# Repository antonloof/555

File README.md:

# 555 timer

A (or two actully) 555 timer made from some junk found in drawers

Could become a future "learn to PCB" project

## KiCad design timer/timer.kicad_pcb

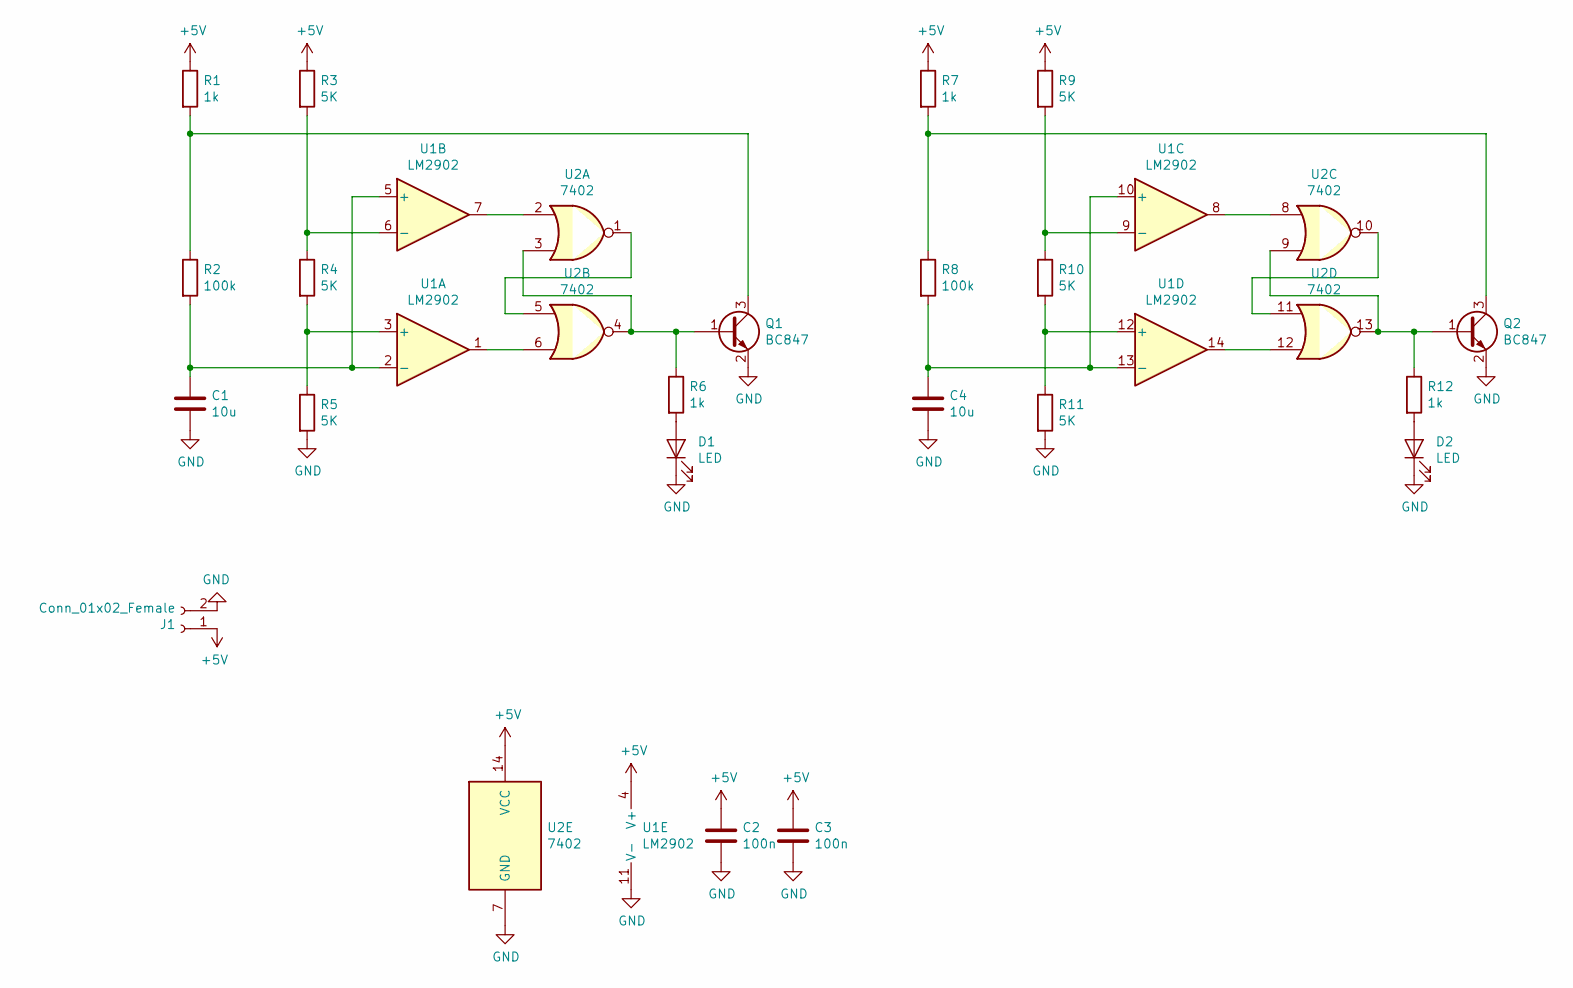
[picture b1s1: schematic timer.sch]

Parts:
C1, C4: 10u; C_0805_2012Metric_Pad1.15x1.40mm_HandSolder
C2, C3: 100n; C_0805_2012Metric_Pad1.15x1.40mm_HandSolder
D1, D2: LED; LED_1206_3216Metric_Pad1.42x1.75mm_HandSolder
J1: Conn_01x02_Female; TerminalBlock_Altech_AK300-2_P5.00mm
Q1, Q2: BC847; SOT-323_SC-70_Handsoldering
R1, R6, R7, R12: 1k; C_0805_2012Metric_Pad1.15x1.40mm_HandSolder
R2, R8: 100k; C_0805_2012Metric_Pad1.15x1.40mm_HandSolder
R3, R4, R5, R9, R10, R11: 5K; C_0805_2012Metric_Pad1.15x1.40mm_HandSolder
U1: LM2902; TSSOP-14_4.4x5mm_P0.65mm
U2: 7402; DIP-14_W7.62mm

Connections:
+5V: C2.1, C3.1, J1.1, R1.1, R3.1, R7.1, R9.1, U1.4 (V+), U2.14 (VCC)
GND: C1.2, C2.2, C3.2, C4.2, D1.1 (K), D2.1 (K), J1.2, Q1.2 (E), Q2.2 (E), R5.2, R11.2, U1.11 (V-), U2.7 (GND)
unnamed: C1.1, R2.2, U1.2 (-), U1.5 (+)
unnamed: C4.1, R8.2, U1.10 (+), U1.13 (-)
unnamed: D1.2 (A), R6.2
unnamed: D2.2 (A), R12.2
unnamed: Q1.1 (B), R6.1, U2.3, U2.4
unnamed: Q1.3 (C), R1.2, R2.1
unnamed: Q2.1 (B), R12.1, U2.9, U2.13
unnamed: Q2.3 (C), R7.2, R8.1
unnamed: R3.2, R4.1, U1.6 (-)
unnamed: R4.2, R5.1, U1.3 (+)
unnamed: R9.2, R10.1, U1.9 (-)
unnamed: R10.2, R11.1, U1.12 (+)
unnamed: U1.1, U2.6
unnamed: U1.7, U2.2
unnamed: U1.8, U2.8
unnamed: U1.14, U2.12
unnamed: U2.1, U2.5
unnamed: U2.10, U2.11

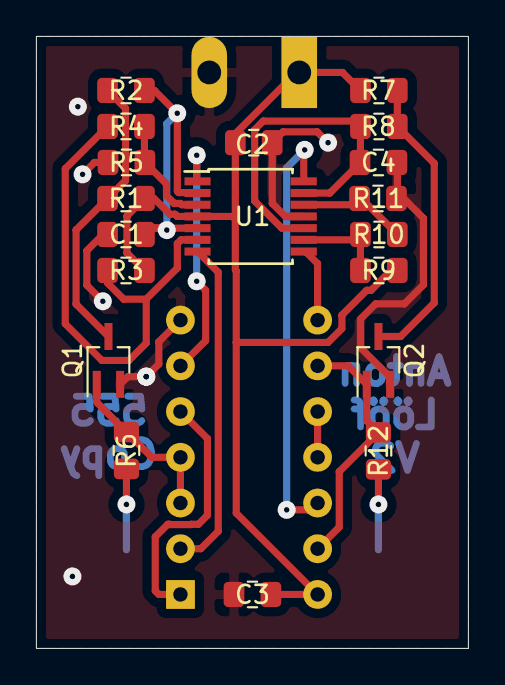
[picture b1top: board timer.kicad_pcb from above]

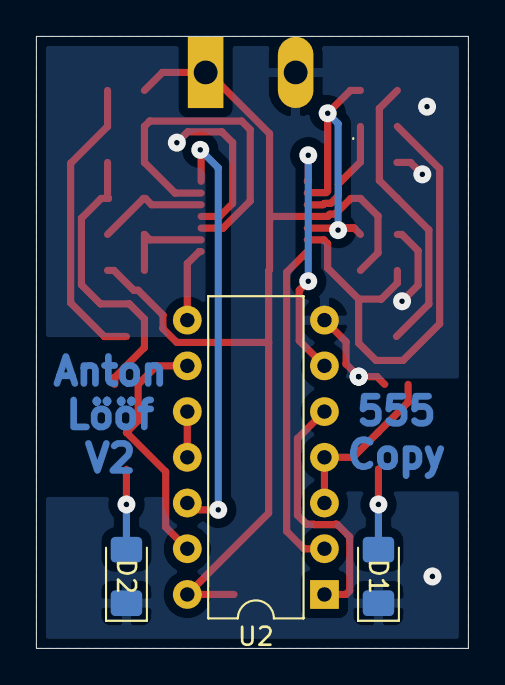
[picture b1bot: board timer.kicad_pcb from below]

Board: 2 copper layers, 24.0 x 34.0 mm, 23 parts (4 on the bottom side), 20 nets.

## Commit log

2021-03-27 v1 pcb
2021-03-27 Start using opamp that can ouput stuff
2021-03-27 Finalize rev2 pcb
